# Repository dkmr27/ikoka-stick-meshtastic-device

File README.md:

# Ikoka Stick Meshtastic Device

This is a modified version of the Ikoka for E22 or E22P, selectable via solder pad jumper.
Please use E22 Meshcore firmware for the E22P modules, do not use a E22P version of firmware, the switching differences are handled in hardware for this board.

## Ikoka! (行こか!)

“行こか?” or “行こか!” is [Kansai dialect](https://en.wikipedia.org/wiki/Kansai_dialect) for “shall we go?” or “let’s go!”.

I hope that building these long-range Meshtastic designs inspires you to go on your next [DXing](https://en.wikipedia.org/wiki/DXing) adventure.

## Features

- LoRa
  - Up to 33 dBm (2 W) output power
  - 410–493 MHz (433 MHz band) or 850–930 MHz (868/915/923 MHz band)
- Bluetooth 5 LE
- Wi-Fi 4 (2.4 GHz)
- Lithium-ion battery with charging
- 0.96" OLED display

Feature set above depends on part selection.

### Hardware

### Parts Selection

Several options are available depending on the feature set you need.

#### Microcontroller

- [Seeed Studio XIAO-nRF52840](https://www.seeedstudio.com/Seeed-XIAO-BLE-nRF52840-p-5201.html) - Bluetooth 5/LE
- [Seeed Studio XIAO-ESP32-S3](https://www.seeedstudio.com/XIAO-ESP32S3-p-5627.html) - Bluetooth 5/LE and Wi-Fi 4 (2.4 GHz)

#### LoRa Module

- [E22-400M22S](https://www.cdebyte.com/products/E22-400M22S) (410–493 MHz at 22 dBm)
- [E22-400M30S](https://www.cdebyte.com/products/E22-400M30S) (410–493 MHz at 30 dBm)
- [E22-400M33S](https://www.cdebyte.com/products/E22-400M33S) (410–493 MHz at 33 dBm)
- [E22-900M22S](https://www.cdebyte.com/products/E22-900M22S) (850–930 MHz at 22 dBm)
- [E22-900M30S](https://www.cdebyte.com/products/E22-900M30S) (850–930 MHz at 30 dBm)
- [E22-900M33S](https://www.cdebyte.com/products/E22-900M33S) (850–930 MHz at 33 dBm)

#### Lithium-ion Battery (4.2V charging termination, optional)

- 21700 Lithium-ion battery cell (4.2V charge termination; holder: [BeilaMoo PA21700*1-SMT](https://www.beilamoo.com/sdm/1074412/4/pd-5180803/21061576-2986071/ONE_21700_Battery_Holder_with_Surface_Mount_SMT.html)/[MYOUNG BH-21700-B1BJ001](https://jlcpcb.com/partdetail/Myoung-BH_21700B1BJ001/C20606791))
- Lithium-polymer pouch battery cell (4.2V charge termination; connector: Molex PicoBlade 1x02P, pitch 1.25mm)
- Do not use both a 21700 and LiPo battery simultaneously, they will be shorted together in parallel

##### Wiring for Battery Charging

You will need a PicoBlade Female-to-Pigtail cable assembly such as Molex [218112-0200](https://www.molex.com/en-us/products/part-detail/2181120200). A compatible cable ships with Heltec Wireless and LILYGO LoRa products so you probably have spares you can use. [Muzi Works](https://muzi.works/products/battery-cable-molex-picoblade) and [Rokland](https://store.rokland.com/products/battery-connector-cables-battery-wires-jst-1-25-5pcs-for-lilygo-and-heltec) also sell compatible cables.

1. Trim the pigtail length to around 5cm if it is longer
2. Strip 2mm of insulation from each pigtail, then twist and tin the wire strands
3. Solder the red pigtail (or pin 1) to the BAT+ pad on the back of the XIAO module
4. Solder the black pigtail (or pin 2) to the BAT- pad on the back of the XIAO module
5. Plug the cable into the XIAO Charger connector on the Ikoka Stick

In my previous design, the [Ikoka Nano](https://github.com/ndoo/ikoka-nano-meshtastic-device), the XIAO module was SMD soldered onto the board, while the BAT+ pad was soldered through a plated through-hole via. However, the actual solder joint is buried and couldn't be inspected for continuity, quality and ensuring the BAT+ pad was not shorted to the BAT- pad.

In the interest of ease-of-assembly and keeping the XIAO module interchangeable, while not wasting the built-in battery charging circuit on XIAO modules, this approach was chosen instead.

#### OLED Display (Optional)

- Generic SSD1306 0.96" OLED display modules with 2.54mm pin headers [https://www.aliexpress.com/item/1005008077705181.html]((AliExpress))

## Firmware

### GPIO Assignment

| XIAO Pin | Function | XIAO-nRF52840 | XIAO-ESP32-S3 |
|---|---|---|---|
| 1 (D0) | User button | 2 (P0.02) | 1 |
| 2 (D1) | EBYTE E22 - DIO1 | 3 (P0.03) | 2 |
| 3 (D2) | EBYTE E22 - RST | 28 (P0.28) | 3 |
| 4 (D3) | EBYTE E22 - BUSY | 29 (P0.29) | 4 |
| 5 (D4) | EBYTE E22 - SPI NSS | 4 (P0.04) | 5 |
| 6 (D5) | EBYTE E22 - RXEN | 5 (P0.05) | 6 |
| 7 (D6) | SSD1306 OLED - I2C SDA | 43 (P1.11) | 43 |
| 8 (D7) | SSD1306 OLED - I2C SCL | 44 (P1.12) | 44 |
| 9 (D8) | EBYTE E22 - SPI SCK | 45 (P1.13) | 7 |
| 10 (D9) | EBYTE E22 - SPI MISO | 46 (P1.14) | 8 |
| 11 (D10) | EBYTE E22 - SPI MOSI | 47 (P1.15) | 9 |
| 12 | SSD1306 OLED - 3.3V | 3V3 | 3V3 |
| 13 | GND | GND | GND |
| 14 | NC | 5V | 5V |

### Meshtastic Compatibility

The XIAO module is intended to be socketed with pin headers/pin sockets, to allow swapping out modules depending on what features are needed (Bluetooth, Wi-Fi, different power consumption profiles, etc.); Compatibility with official Meshtastic firmware depends on the inserted XIAO board.

#### XIAO-nRF52840

- EBYTE E22 LoRa
  - LoRa pins are identical to the officially-supported [Seeed Xiao NRF52840 Kit](https://www.seeedstudio.com/XIAO-nRF52840-Wio-SX1262-Kit-for-Meshtastic-p-6400.html) on [Meshtastic Web Flasher](https://flasher.meshtastic.org/)
  - LoRa will work out of the box on officially-supported firmware
  - Special consideration must be taken if using the E22-900M33S module
    - Set the transmit power to ≤ 9 dBm on first use (when setting the LoRa region)
    - **Transmit power must never be set greater than 9 dBm*- to avoid damaging the module's RF frontend
- SSD1306 OLED I2C
  - Pin D6/P1.11 and D7/P1.12 are [reserved for the L76K GPS module in the officially-supported variant](https://github.com/meshtastic/firmware/blob/152b8b1b0235bc461c6e4451fbcdac0987b8bf90/variants/seeed_xiao_nrf52840_kit/variant.h#L137-L138)
  - A custom firmware must be built to define these pins as I2C (TODO)
- User button
  - Pin D0/P0.02 is [reserved for the L76K GPS module in the officially supported variant](https://github.com/meshtastic/firmware/blob/152b8b1b0235bc461c6e4451fbcdac0987b8bf90/variants/seeed_xiao_nrf52840_kit/variant.h#L144)
  - A custom firmware must be built to define this pin as the user button (TODO)

### XIAO-ESP32-S3

- Pin definitions are different from the officially-supported [Seeed Xiao ESP32-S3 Kit](https://www.seeedstudio.com/Wio-SX1262-with-XIAO-ESP32S3-p-5982.html)
  - This is because Seeed uses GPIOs on the 30-pin board-to-board press-fit connector instead of the standard XIAO pins
  - A custom firmware must be built (TODO)

## PCB Renders

### PCB Top

### PCB Bottom

### Rotating GIF

(Rendered with [kicad-render](https://github.com/linalinn/kicad-render).)

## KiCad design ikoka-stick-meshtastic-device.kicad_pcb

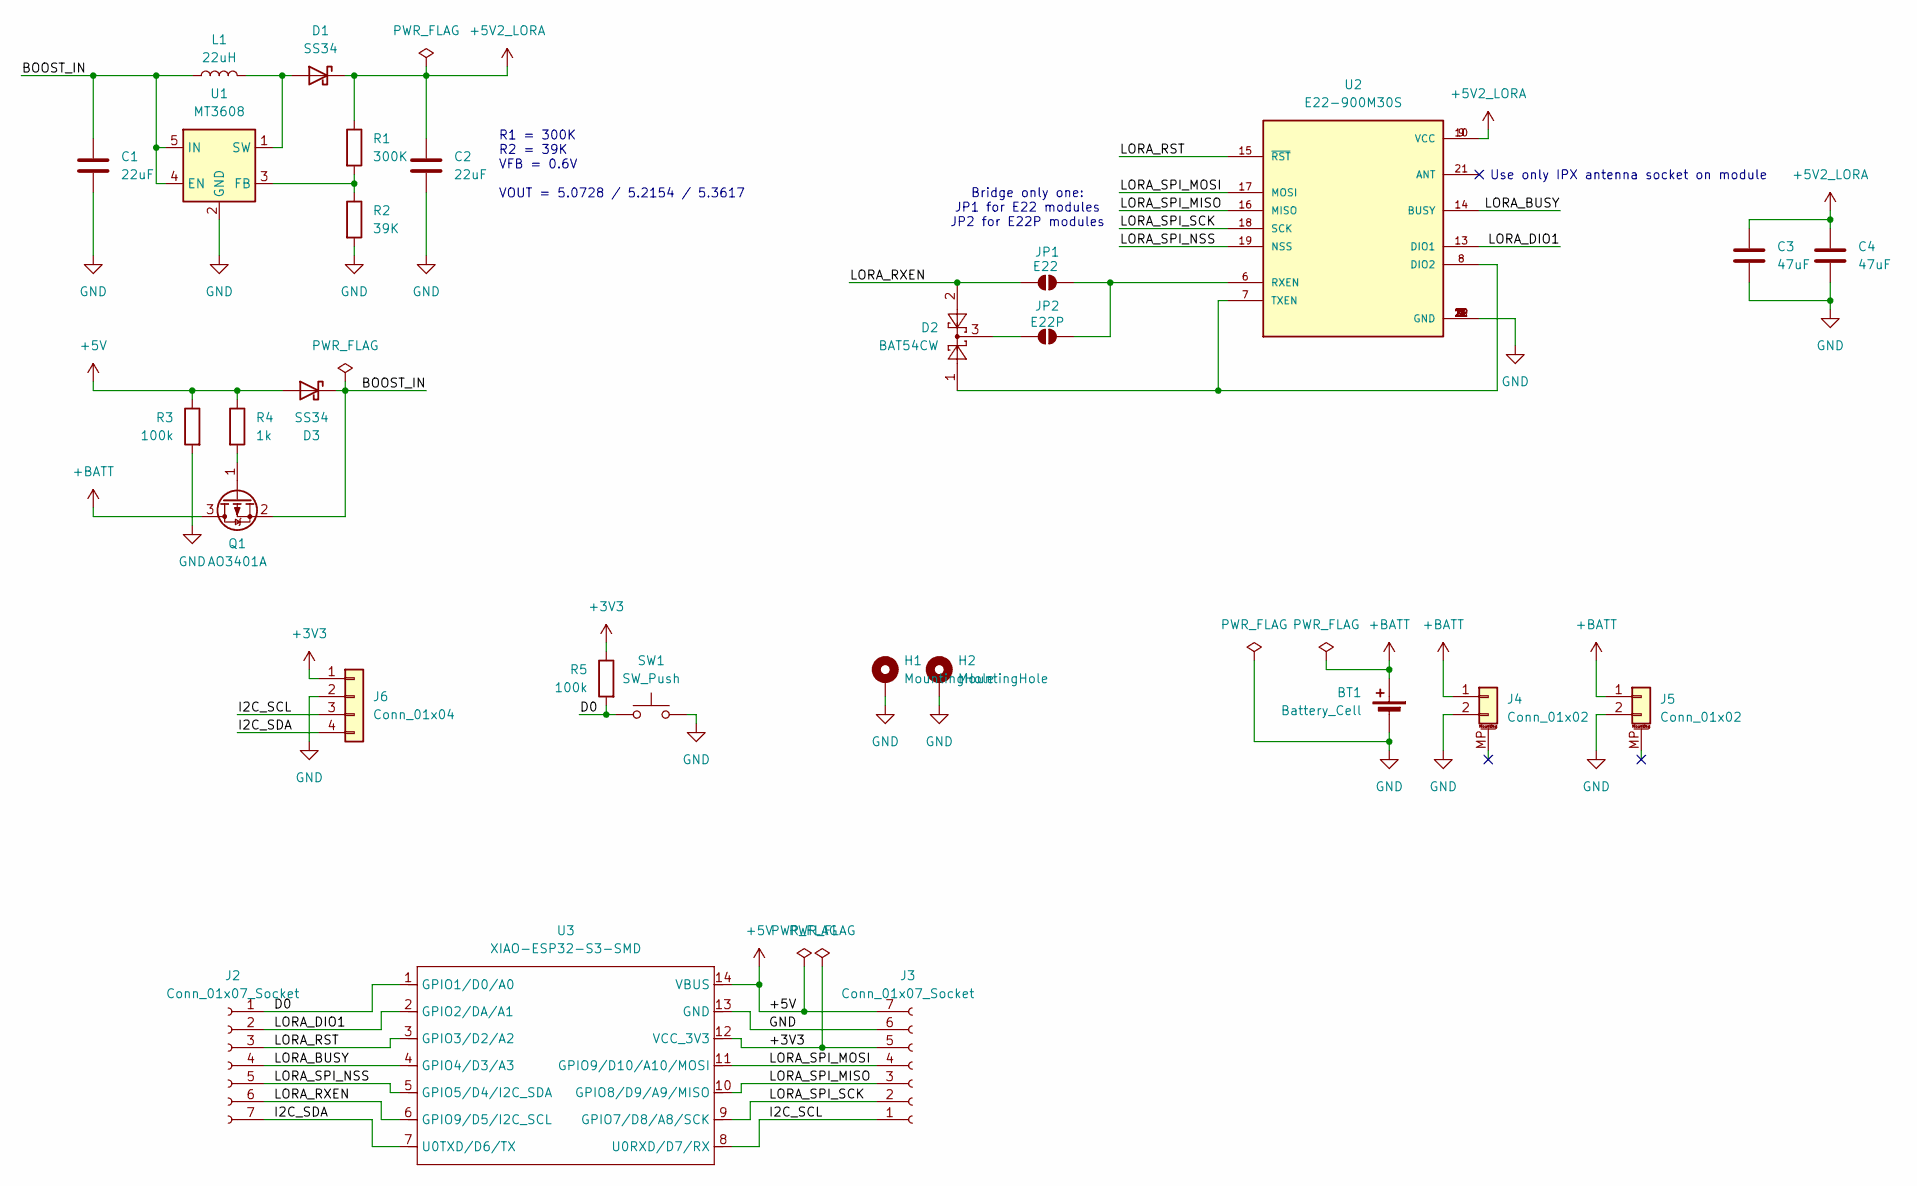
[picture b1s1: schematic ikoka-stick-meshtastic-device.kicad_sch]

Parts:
BT1: Battery_Cell; BatteryHolder_MYOUNG_BH-21700-B1BJ001_1x21700; LCSC C20606791
C1, C2: 22uF; C_0603_1608Metric; LCSC C59461
C3, C4: 47uF; C_0805_2012Metric; LCSC C16780
D1, D3: SS34; D_SMA; LCSC C8678
D2: BAT54CW; SOT-323_SC-70; LCSC C82467
H1, H2: MountingHole; MountingHole_2.2mm_M2_Pad_Via
J2, J3: Conn_01x07_Socket; PinSocket_1x07_P2.54mm_Vertical_SMD_Pin1Left; LCSC C42379199
J4, J5: Conn_01x02; Molex_PicoBlade_53261-0271_1x02-1MP_P1.25mm_Horizontal; LCSC C2905009
J6: Conn_01x04; PinSocket_1x04_P2.54mm_Vertical_SMD_Pin1Right; LCSC C46635840
JP1: E22; SolderJumper-2_P1.3mm_Open_RoundedPad1.0x1.5mm
JP2: E22P; SolderJumper-2_P1.3mm_Open_RoundedPad1.0x1.5mm
L1: 22uH; L_Sunlord_MWSA0624S; LCSC C408436
Q1: AO3401A; SOT-23; LCSC C15127
R1: 300K; R_0603_1608Metric; LCSC C23024
R2: 39K; R_0603_1608Metric; LCSC C23153
R3, R5: 100k; R_0603_1608Metric; LCSC C25803
R4: 1k; R_0603_1608Metric; LCSC C21190
SW1: SW_Push; SW_Push_1P1T_XKB_TS-1187A; LCSC C318884
U1: MT3608; SOT-23-6; LCSC C2932326
U2: E22-900M30S; XCVR_E22-900M30S_NO_ANT; PARTREV 1.2; LCSC C411294
U3: XIAO-ESP32-S3-SMD; XIAO-ESP32S3-DIP; LCSC C9900124959

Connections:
+3V3: J3.5, J6.1, R5.1, U3.12 (VCC_3V3)
+5V: D3.2 (A), J3.7, R3.1, R4.1, U3.14 (VBUS)
+5V2_LORA: C2.1, C3.1, C4.1, D1.1 (K), R1.1, U2.9 (VCC), U2.10 (VCC)
+BATT: BT1.1 (+), J4.1, J5.1, Q1.3 (D)
/BOOST_IN: C1.1, D3.1 (K), L1.2, Q1.2 (S), U1.4 (EN), U1.5 (IN)
/D0: J2.1, R5.2, SW1.1, U3.1 (GPIO1/D0/A0)
/I2C_SCL: J3.1, J6.3, U3.8 (U0RXD/D7/RX)
/I2C_SDA: J2.7, J6.4, U3.7 (U0TXD/D6/TX)
/LORA_BUSY: J2.4, U2.14 (BUSY), U3.4 (GPIO4/D3/A3)
/LORA_DIO1: J2.2, U2.13 (DIO1), U3.2 (GPIO2/DA/A1)
/LORA_RST: J2.3, U2.15 (~RST), U3.3 (GPIO3/D2/A2)
/LORA_RXEN: D2.2, J2.6, JP1.1 (A), U3.6 (GPIO9/D5/I2C_SCL)
/LORA_SPI_MISO: J3.3, U2.16 (MISO), U3.10 (GPIO8/D9/A9/MISO)
/LORA_SPI_MOSI: J3.4, U2.17 (MOSI), U3.11 (GPIO9/D10/A10/MOSI)
/LORA_SPI_NSS: J2.5, U2.19 (NSS), U3.5 (GPIO5/D4/I2C_SDA)
/LORA_SPI_SCK: J3.2, U2.18 (SCK), U3.9 (GPIO7/D8/A8/SCK)
GND: BT1.2 (-), C1.2, C2.2, C3.2, C4.2, H1.1, H2.1, J3.6, J4.2, J5.2, J6.2, R2.2, R3.2, SW1.2, U1.2 (GND), U2.1 (GND), U2.2 (GND), U2.3 (GND), U2.4 (GND), U2.5 (GND), U2.11 (GND), U2.12 (GND), U2.20 (GND), U2.22 (GND), U3.13 (GND)
unnamed: D1.2 (A), L1.1, U1.1 (SW)
unnamed: JP1.2 (B), JP2.2 (B), U2.6 (RXEN)
unnamed: D2.3, JP2.1 (A)
unnamed: Q1.1 (G), R4.2
unnamed: R1.2, R2.1, U1.3 (FB)
unnamed: D2.1, U2.7 (TXEN), U2.8 (DIO2)

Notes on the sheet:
Bridge only one: JP1 for E22 modules JP2 for E22P modules
R1 = 300K R2 = 39K VFB = 0.6V VOUT = 5.0728 / 5.2154 / 5.3617
Use only IPX antenna socket on module

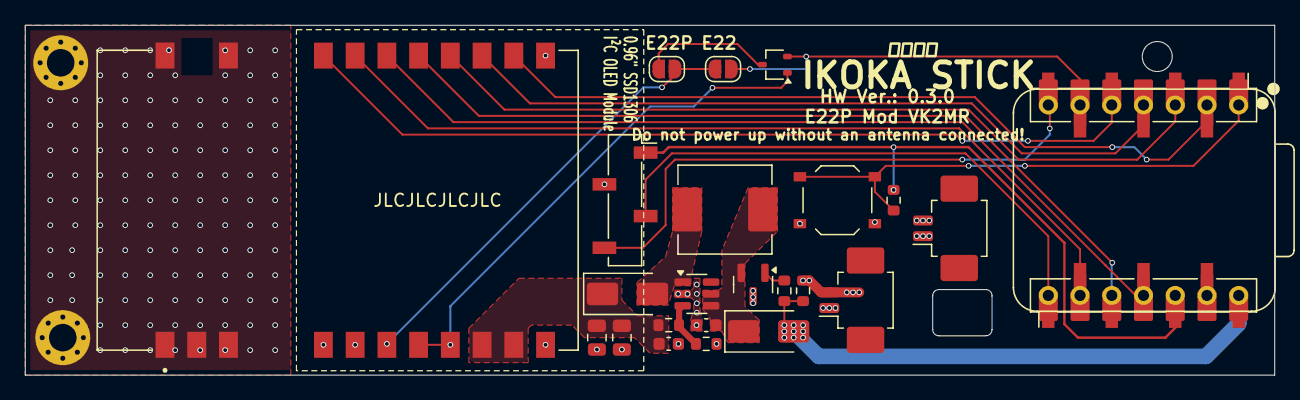
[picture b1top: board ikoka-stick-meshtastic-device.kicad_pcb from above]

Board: 2 copper layers, 100.0 x 28.0 mm, 28 parts (1 on the bottom side), 23 nets.

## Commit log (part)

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2025-11-27 Modification to support E22P modules
